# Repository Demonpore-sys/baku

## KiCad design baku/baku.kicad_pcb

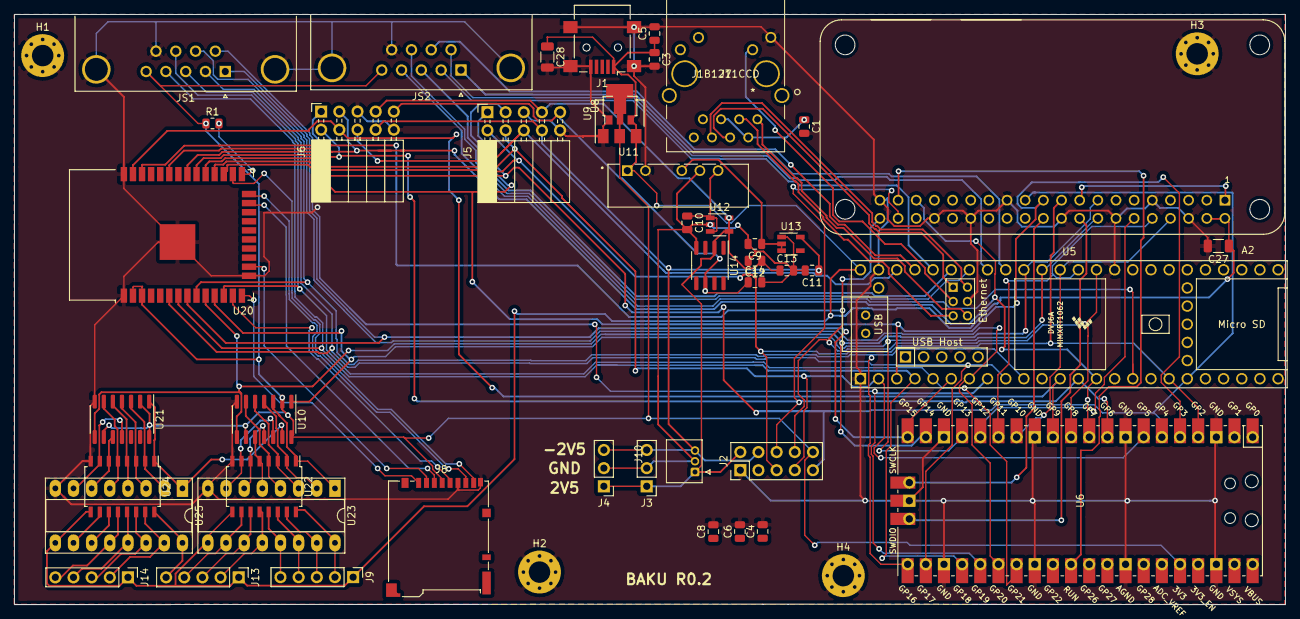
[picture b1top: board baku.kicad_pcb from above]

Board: 2 copper layers, 177.8 x 82.6 mm, 49 parts (0 on the bottom side), 82 nets.

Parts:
A2: ADA3708; ADA3708_RPI-ZERO
C1, C4, C6: 0.1uF; C_0805_2012Metric
C3, C5, C8: 10uF; C_0805_2012Metric
C9, C10, C11, C12: 2.2uF; C_0805_2012Metric
C13: 1uF; C_0805_2012Metric
C14: 22uF; C_0805_2012Metric
C27, C28: CP1_Small; C_1206_3216Metric
H1, H2, H3, H4: MountingHole_Pad; MountingHole_3mm_Pad_Via
J1: USB_B_Mini; USB_Mini-B_Lumberg_2486_01_Horizontal
J2: Conn_02x05_Odd_Even; PinHeader_2x05_P2.54mm_Vertical
J3, J4: Conn_01x03; PinHeader_1x03_P2.54mm_Vertical
J5, J6: Conn_02x05_Odd_Even; PinSocket_2x05_P2.54mm_Horizontal
J7: J1B1211CCD
J8: Micro_SD_Card; microSD_HC_Hirose_DM3BT-DSF-PEJS
J9, J13, J14: Conn_01x05_Male; PinHeader_1x05_P2.54mm_Vertical
J10: Conn_01x03; JST
JS1, JS2: DB9_Male_MountingHoles; DSUB-9_Male_Horizontal_P2.77x2.84mm_EdgePinOffset4.94mm_Hou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
R1: 10K; R_0805_2012Metric
U5: Teensy4.1; Teensy41
U6: Pico; RPi_Pico_SMD_TH
U8: AZ1117-3.3; SOT-89-3
U9: AZ1117-3.3; SOT-223-3_TabPin2
U10, U21: 74HC164; SOIC-14_3.9x8.7mm_P1.27mm
U11: PDME1-S5-D3-S; CONV_PDME1-S5-D3-S
U12: ADP7142AUJZ-2.5; TSOT-23-5
U13: ADP7182AUJZ-2.5; TSOT-23-5
U14: REF5020AD; SOIC-8_3.9x4.9mm_P1.27mm
U20: ESP32-WROOM-32
U22, U24: ULN2003A; SOIC-16W_5.3x10.2mm_P1.27mm
U23, U25: ULN2003A; DIP-16_W7.62mm_Socket_LongPads

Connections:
/2V5: C12.1, C13.1, J2.2, J3.1, J4.1, J5.7, J6.7, J10.1, U12.4, U12.5, U14.2
/3V3: C4.1, C6.1, C8.1, J2.10, J8.4, JS1.5, JS2.5, R1.1, U6.36, U8.2, U9.2, U10.2, U10.9, U10.14, U20.2, U20.3, U21.2, U21.9, U21.14
/5V: A2.2, A2.4, C3.1, C5.1, C27.1, C28.1, J1.1, J9.1, J13.1, J14.1, U5.48, U8.3, U9.3, U11.1, U22.9, U23.9, U24.9, U25.9
/-2V5: C11.1, J2.4, J3.3, J4.3, J5.8, J6.8, J10.3, U13.5
/A_BUTTON1: JS1.6, U5.8, U6.25
/A_BUTTON2: JS1.4, U5.4, U6.24, U20.7
/A_DOWN: JS1.2, U5.10, U6.21, U20.9
/A_LEFT: JS1.3, U5.9, U6.22, U20.6
/A_RIGHT: JS1.7, U5.7, U6.26
/A_SWITCH_COMMON: JS1.8, U5.5, U6.27, U20.12
/A_UP: JS1.1, U5.6, U6.20, U20.8
/B_BUTTON1: JS2.6, U5.41
/B_BUTTON2: JS2.7, U5.45
/B_DOWN: JS2.2, U5.44
/B_LEFT: JS2.4, U5.16
/B_RIGHT: JS2.3, U5.43
/B_SWITCH_COMMON: JS2.8, U5.42
/B_UP: JS2.1, U5.40
/DAC_LDAC: J2.7, J5.4, U5.2, U6.7, U20.30
/ESP32_with_cam/SD_CLK: J8.5, U20.13
/ESP32_with_cam/SD_CMD: J8.3, U20.23
/ESP32_with_cam/SD_DAT0: J8.7, U20.24
/ESP32_with_cam/SD_DAT1: J8.8, U20.26
/ESP32_with_cam/SD_DAT2: J8.1, U20.14
/ESP32_with_cam/SD_DAT3: J8.2, U20.16
/GNDA: C9.2, C10.2, C11.2, C12.2, C13.2, C14.2, J3.2, J4.2, J10.2, U11.5, U12.2, U13.1, U14.4
/IOREF: J5.6, J6.6, U5.46
/REF: C14.1, J5.9, J6.9, U14.6
/RPI_3V3: A2.1, A2.17
/RPI_GPIO24: A2.18, U6.43
/RPI_GPIO25: A2.22, U6.41
/RPI_GPIO26: A2.37, U6.30
/RPI_SPI1_CE0: A2.12, U6.16
/RPI_UART_RX: A2.10, U5.36, U6.15
/RPI_UART_TX: A2.8, U5.37, U6.14
/SPI1_MISO: A2.21, J5.3, U5.3, U6.5, U20.27
/SPI1_MOSI: A2.19, J2.5, J5.2, U5.18, U6.4, U20.29
/SPI1_SCLK: A2.23, J2.9, J5.1, U5.19, U6.6, U20.28
/SPI4_CS0: J6.4, U5.12, U6.12, U20.37
/SPI4_MISO: A2.35, J6.3, U5.14, U6.10, U20.33
/SPI4_MOSI: A2.38, J2.6, J6.2, U5.13, U6.9, U20.31
/SPI4_SCLK: A2.40, J2.8, J6.1, U5.35, U6.11, U20.36
/STEP_CLK: A2.15, U5.39, U6.19, U10.8, U20.10, U21.8
/STEP_SIGNAL: A2.16, U5.38, U6.17, U10.1, U20.11
/steppers/EXTRA_OUT1: U24.11, U25.11
/steppers/EXTRA_OUT2: U24.10, U25.10
GND: A2.6, A2.9, A2.14, A2.20, A2.25, A2.30, A2.34, A2.39, C1.2, C3.2, C4.2, C5.2, C6.2, C8.2, C27.2, C28.2, H1.1, H2.1, H3.1, H4.1, J1.5, J1.6, J2.1, J5.5, J5.10, J6.5, J6.10, J7.9, J8.6, J8.9, JS1.0, JS1.9, JS2.0, JS2.9, U5.1, U5.34, U5.47, U5.64, U6.3, U6.8, U6.13, U6.18, U6.23, U6.28, U6.33, U6.38, U6.42, U8.1, U9.1, U10.7, U11.2, U20.1, U20.15, U20.38, U20.39, U21.7, U22.8, U23.8, U24.8, U25.8
LED: J7.10, U5.61
unnamed: C1.1, J7.2, J7.5
unnamed: C9.1, U11.4, U13.2, U13.3
unnamed: C10.1, U11.6, U12.1, U12.3
unnamed: J9.2, U22.16, U23.16
unnamed: J9.3, U22.15, U23.15
unnamed: J9.4, U22.14, U23.14
unnamed: J9.5, U22.13, U23.13
unnamed: J13.2, U22.12, U23.12
unnamed: J13.3, U22.11, U23.11
unnamed: J13.4, U22.10, U23.10
unnamed: J13.5, U24.16, U25.16
unnamed: J14.2, U24.15, U25.15
unnamed: J14.3, U24.14, U25.14
unnamed: J14.4, U24.13, U25.13
unnamed: J14.5, U24.12, U25.12
unnamed: R1.2, U20.25
unnamed: U10.3, U22.1, U23.1
unnamed: U10.4, U22.2, U23.2
unnamed: U10.5, U22.3, U23.3
unnamed: U10.6, U22.4, U23.4
unnamed: U10.10, U22.5, U23.5
unnamed: U10.11, U22.6, U23.6
unnamed: U10.12, U22.7, U23.7
unnamed: U10.13, U21.1, U24.1, U25.1
unnamed: U21.3, U24.2, U25.2
unnamed: U21.4, U24.3, U25.3
unnamed: U21.5, U24.4, U25.4
unnamed: U21.6, U24.5, U25.5
unnamed: U21.10, U24.6, U25.6
unnamed: U21.11, U24.7, U25.7
R+: J7.4, U5.60
R-: J7.6, U5.65
T+: J7.1, U5.63
T-: J7.3, U5.62

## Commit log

2021-04-16 Adding some boards...
    The pico board came from
    https://github.com/HeadBoffin/RP_Silicon_KiCad
2021-07-19 Attempting to get files into git...
2021-09-26 About to remove the onboard adc/dac
2021-09-27 Maybe version 0.1
2021-09-27 This is perhaps what was just ordered at JLPCB
2022-01-15 Starting in on Rev 0.2
2022-01-15 Using Teensy4.1 sheet...
2022-01-15 Light trace cleanup
2022-01-20 Not completely sure what these changes are
2022-01-20 Fixed plugs for ADC and DAC.. maybe...

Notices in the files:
parts and their libraries:
Copyright 2016 Accelerated Designs. All rights reserved.
